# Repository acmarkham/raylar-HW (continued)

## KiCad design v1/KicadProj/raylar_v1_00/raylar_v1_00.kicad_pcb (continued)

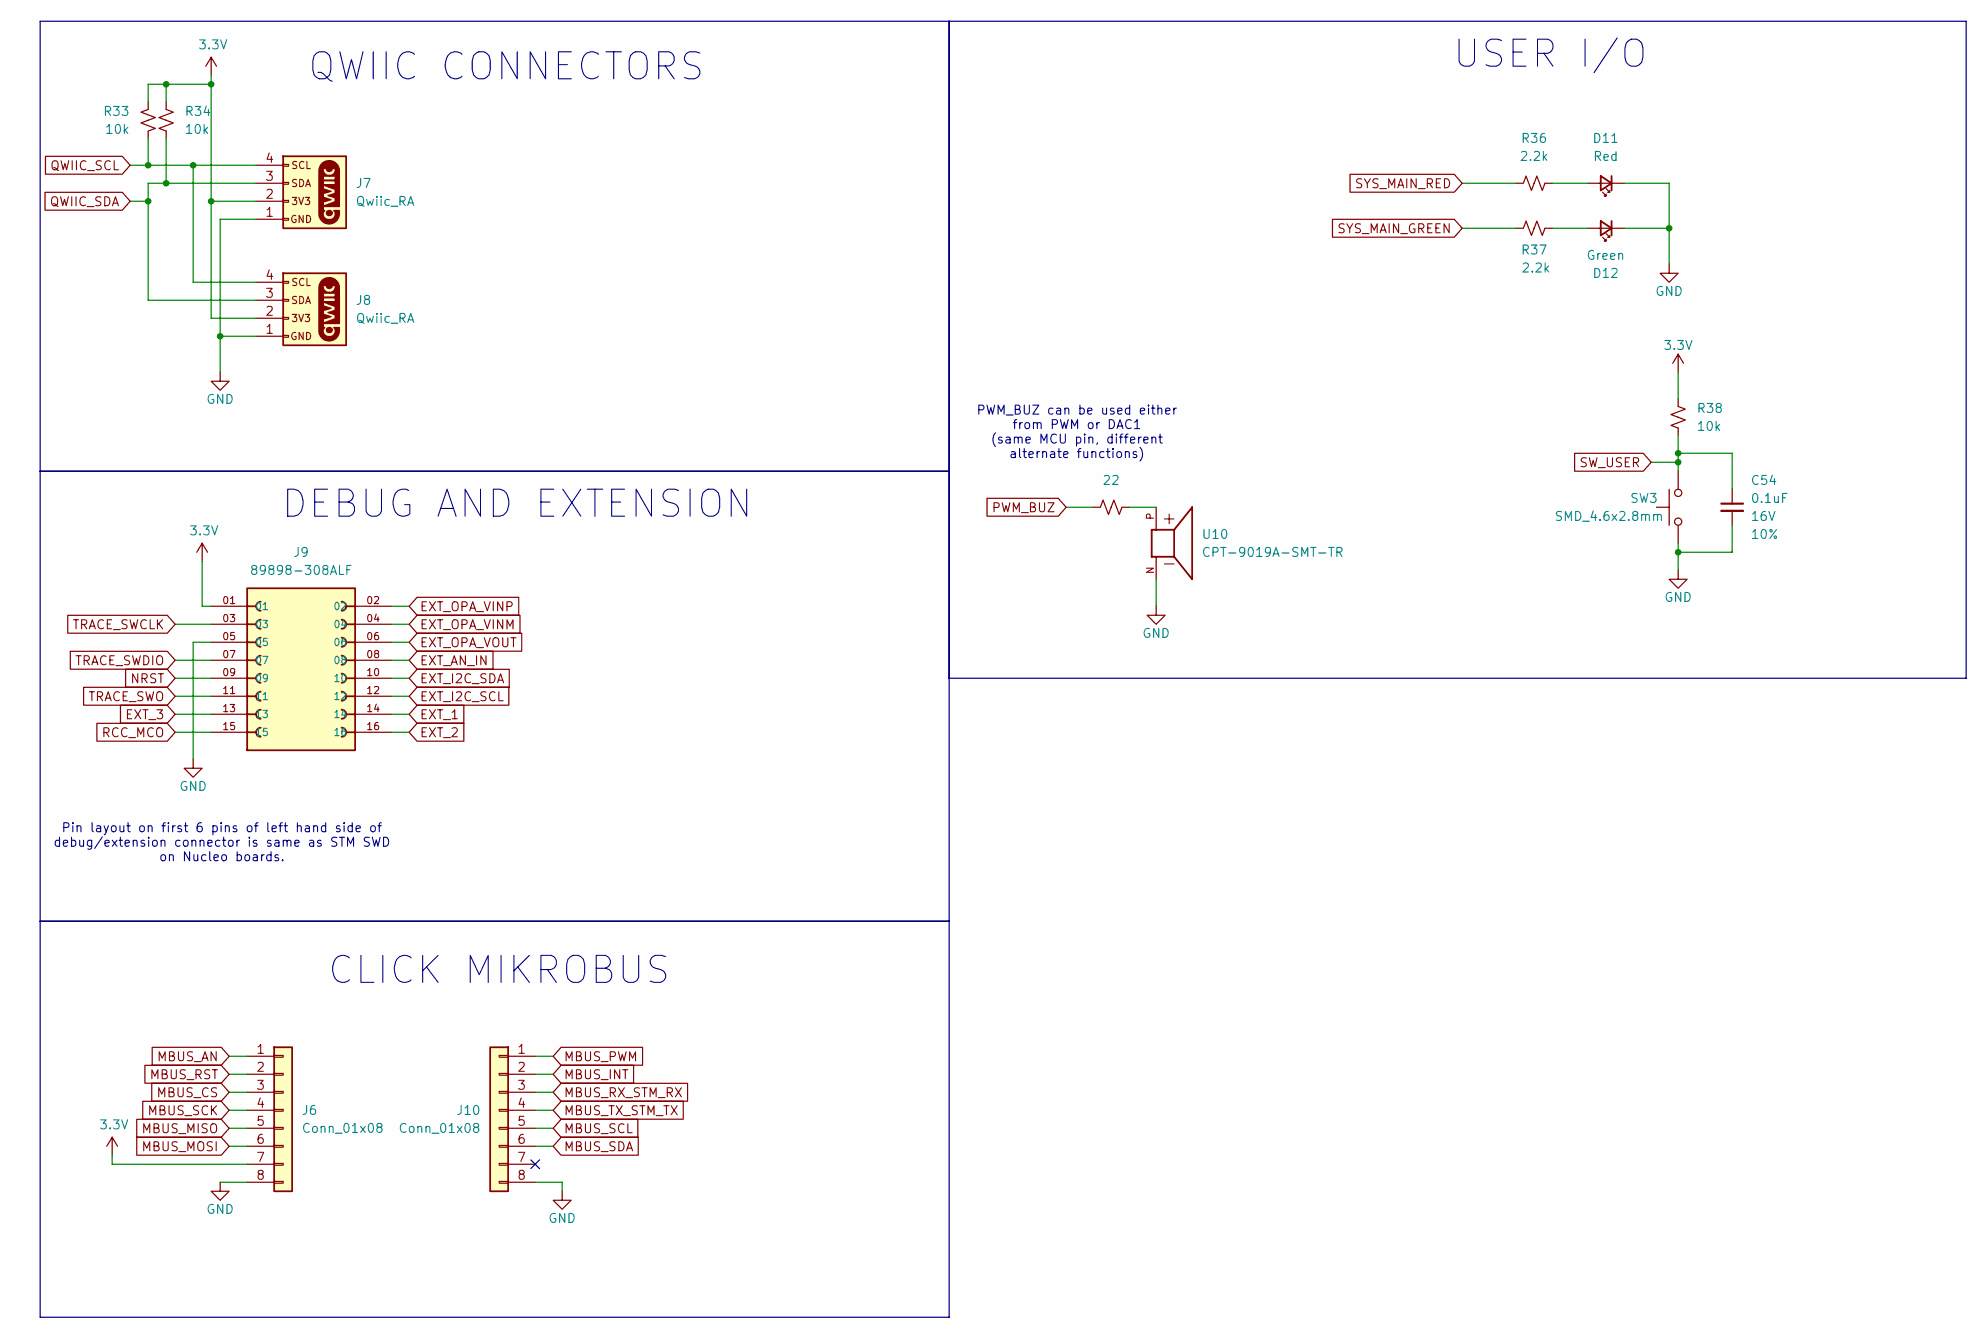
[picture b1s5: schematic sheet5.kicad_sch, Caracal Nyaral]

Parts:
C54: 0.1uF; C_0402_1005Metric; Voltage 16V; Tolerance 10%; LCSC C77020
D11: Red; LED_0603_1608Metric_Red; LCSC C19171390
D12: Green; LED_0603_1608Metric_Green; LCSC C19273151
J6, J10: Conn_01x08; 1x08_P2.54mm_Socket_Vertical_SMD_Pin1RightDown; Digikey 2073-BG125-08-A-1-1-0440-N-D-ND
J7, J8: Qwiic_RA; JST_1x04_P1.0mm_Horizontal_SMD; Digikey 455-SM04B-SRSS-TBDKR-ND
J9: 89898-308ALF; AMPHENOL_89898-308ALF; PARTREV AK; Digikey 609-5158-6-ND
R33, R34, R38: 10k; R_0402_1005Metric; LCSC C60489
R35: 22; R_0402_1005Metric; LCSC C25092
R36, R37: 2.2k; R_0402_1005Metric; LCSC C25879
SW3: SMD_4.6x2.8mm; Push_SMD_4.6x2.8mm_h1.9mm; Mfg Part# KMR231NGLFS; LCSC C221676
U10: CPT-9019A-SMT-TR; XDCR_CPT-9019A-SMT-TR; PARTREV 1.0; LCSC C20181991

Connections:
3.3V: J6.7, J7.2, J8.2, J9.01, R33.2, R34.2, R38.2; also elsewhere on the board
EXT_1: J9.14; also elsewhere on the board
EXT_2: J9.16; also elsewhere on the board
EXT_3: J9.13; also elsewhere on the board
EXT_AN_IN: J9.08; also elsewhere on the board
EXT_I2C_SCL: J9.12; also elsewhere on the board
EXT_I2C_SDA: J9.10; also elsewhere on the board
EXT_OPA_VINM: J9.04; also elsewhere on the board
EXT_OPA_VINP: J9.02; also elsewhere on the board
EXT_OPA_VOUT: J9.06; also elsewhere on the board
GND: C54.2, D11.1 (K), D12.1 (K), J6.8, J7.1, J8.1, J9.05, J10.8, SW3.1, U10.N; also elsewhere on the board
MBUS_AN: J6.1; also elsewhere on the board
MBUS_CS: J6.3; also elsewhere on the board
MBUS_INT: J10.2; also elsewhere on the board
MBUS_MISO: J6.5; also elsewhere on the board
MBUS_MOSI: J6.6; also elsewhere on the board
MBUS_PWM: J10.1; also elsewhere on the board
MBUS_RST: J6.2; also elsewhere on the board
MBUS_RX_STM_RX: J10.3; also elsewhere on the board
MBUS_SCK: J6.4; also elsewhere on the board
MBUS_SCL: J10.5; also elsewhere on the board
MBUS_SDA: J10.6; also elsewhere on the board
MBUS_TX_STM_TX: J10.4; also elsewhere on the board
NRST: J9.09; also elsewhere on the board
unnamed: D11.2 (A), R36.2
unnamed: D12.2 (A), R37.2
unnamed: R35.2, U10.P
PWM_BUZ: R35.1; also elsewhere on the board
QWIIC_SCL: J7.4, J8.4, R33.1; also elsewhere on the board
QWIIC_SDA: J7.3, J8.3, R34.1; also elsewhere on the board
RCC_MCO: J9.15; also elsewhere on the board
SW_USER: C54.1, R38.1, SW3.2; also elsewhere on the board
SYS_MAIN_GREEN: R37.1; also elsewhere on the board
SYS_MAIN_RED: R36.1; also elsewhere on the board
TRACE_SWCLK: J9.03; also elsewhere on the board
TRACE_SWDIO: J9.07; also elsewhere on the board
TRACE_SWO: J9.11; also elsewhere on the board

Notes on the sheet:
Pin layout on first 6 pins of left hand side of debug/extension connector is same as STM SWD on Nucleo boards.
PWM_BUZ can be used either from PWM or DAC1 (same MCU pin, different alternate functions)
DEBUG AND EXTENSION
CLICK MIKROBUS
USER I/O
QWIIC CONNECTORS

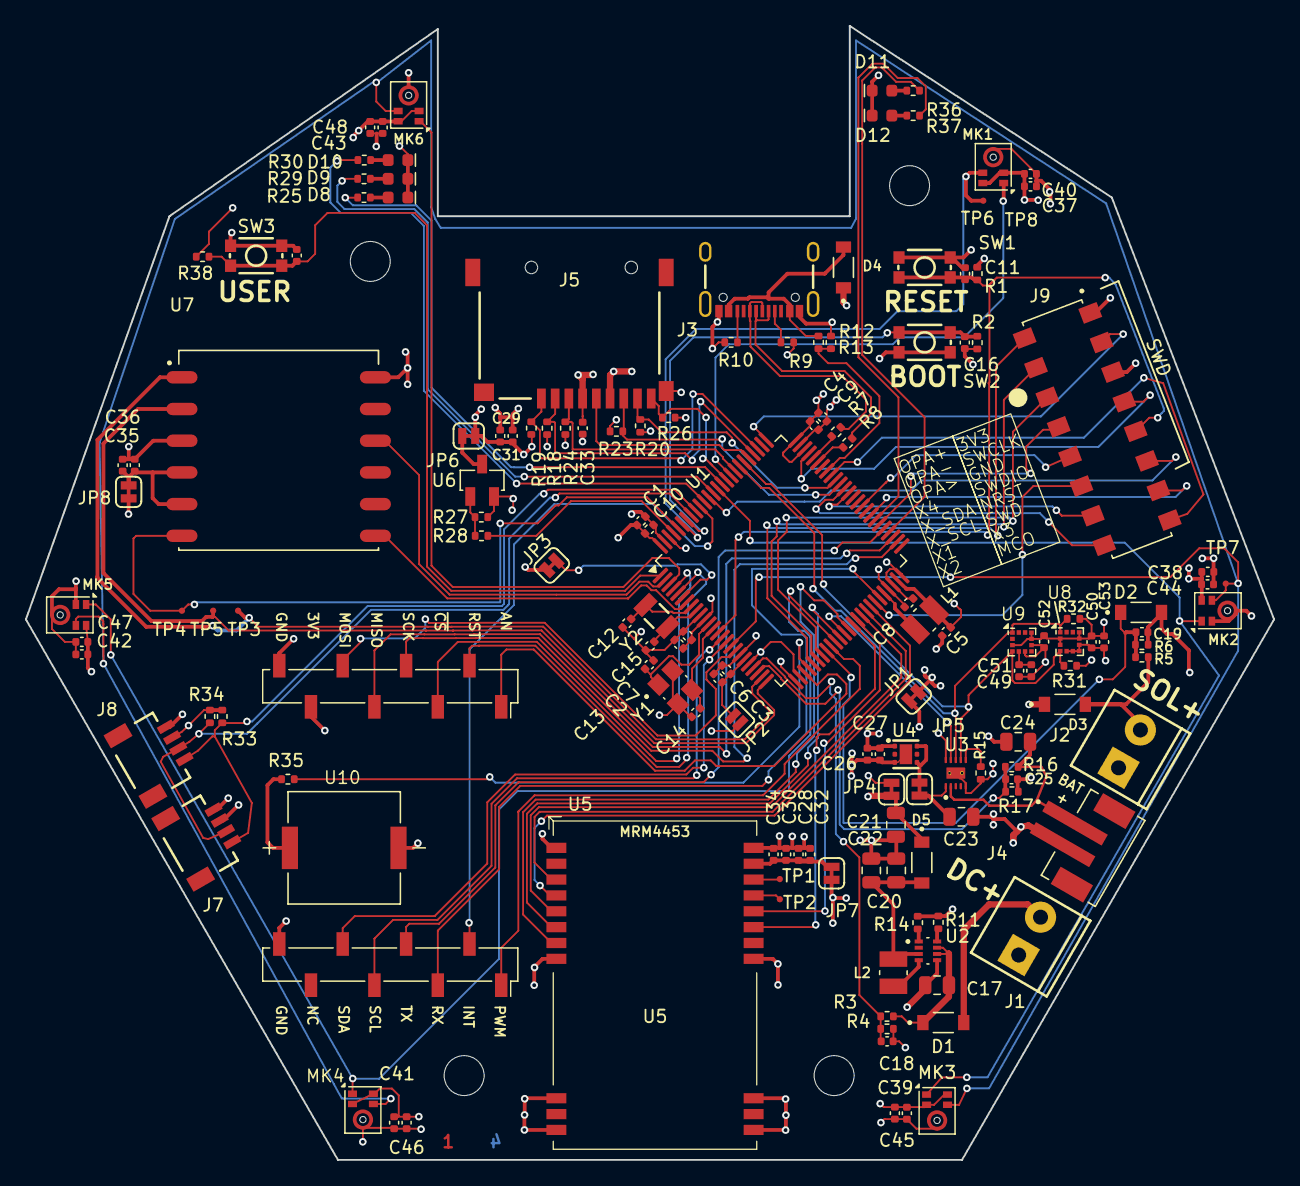
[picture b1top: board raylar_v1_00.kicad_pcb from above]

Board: 4 copper layers, 100.0 x 90.9 mm, 149 parts (0 on the bottom side), 114 nets.

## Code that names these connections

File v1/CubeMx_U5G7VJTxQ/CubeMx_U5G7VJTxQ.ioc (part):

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Mcu.Name=STM32U5G7VJTxQ
Mcu.Package=LQFP100
Mcu.UserName=STM32U5G7VJTxQ
PA0.Mode=IN5-Single-Ended
PA0.Signal=ADC2_IN5
PA1.Mode=IN6-Single-Ended
PA1.Signal=ADC2_IN6
PA11.GPIOParameters=GPIO_Label
PA11.GPIO_Label=USB_DM
PA11.Mode=Internal_Phy_Device
PA11.Signal=USB_OTG_HS_DM
PA12.GPIOParameters=GPIO_Label
PA12.GPIO_Label=USB_DP
PA12.Mode=Internal_Phy_Device
PA12.Signal=USB_OTG_HS_DP
PA13\ (JTMS/SWDIO).GPIOParameters=GPIO_Label
PA13\ (JTMS/SWDIO).GPIO_Label=TRACE_SWDIO
PA13\ (JTMS/SWDIO).Mode=Trace_Asynchronous_SW
PA13\ (JTMS/SWDIO).Signal=DEBUG_JTMS-SWDIO
PA14\ (JTCK/SWCLK).GPIOParameters=GPIO_Label
PA14\ (JTCK/SWCLK).GPIO_Label=TRACE_SWCLK
PA14\ (JTCK/SWCLK).Mode=Trace_Asynchronous_SW
PA14\ (JTCK/SWCLK).Signal=DEBUG_JTCK-SWCLK
PA2.GPIOParameters=GPIO_Label
PA2.GPIO_Label=GPS_RX_STM_TX
PA2.Mode=Asynchronous
PA2.Signal=USART2_TX
PA3.GPIOParameters=GPIO_Label
PA3.GPIO_Label=GPS_TX_STM_RX
PA3.Mode=Asynchronous
PA3.Signal=USART2_RX
PA4.GPIOParameters=GPIO_Label
PA4.GPIO_Label=MBUS_AN
PA4.Mode=IN9-Single-Ended
PA4.Signal=ADC2_IN9
PA5.GPIOParameters=GPIO_Label
PA5.GPIO_Label=BUZ
PA5.Signal=SharedStack_PA5
PA5.Stacked=true
PA6.GPIOParameters=GPIO_Label
PA6.GPIO_Label=EXT_OPA_VINP
PA6.Mode=Standalone
PA6.Signal=OPAMP2_VINP
PA7.GPIOParameters=GPIO_Label
PA7.GPIO_Label=EXT_OPA_VINM
PA7.Mode=Standalone
PA7.Signal=OPAMP2_VINM
PA8.Mode=Clock-out
PA8.Signal=RCC_MCO
PA9.GPIOParameters=GPIO_Label
PA9.GPIO_Label=USB_VBUS
PA9.Mode=Activate_VBUS_FS
PA9.Signal=USB_OTG_HS_VBUS
PB0.GPIOParameters=GPIO_Label
PB0.GPIO_Label=EXT_OPA_VOUT
PB0.Mode=Standalone
PB0.Signal=OPAMP2_VOUT
PB1.Mode=IN16-Single-Ended
PB1.Signal=ADC2_IN16
PB10.GPIOParameters=GPIO_Label
PB10.GPIO_Label=EXT_I2C_SCL
PB10.Mode=I2C
PB10.Signal=I2C4_SCL
PB11.GPIOParameters=GPIO_Label
PB11.GPIO_Label=MBUS_RX_STM_RX
PB11.Mode=Asynchronous
PB11.Signal=USART3_RX
PB13.GPIOParameters=GPIO_Label
PB13.GPIO_Label=MBUS_SCK
PB13.Mode=Full_Duplex_Master
PB13.Signal=SPI2_SCK
PB14.GPIOParameters=GPIO_Label
PB14.GPIO_Label=MBUS_MISO
PB14.Mode=Full_Duplex_Master
PB14.Signal=SPI2_MISO
PB2.GPIOParameters=GPIO_Label
PB2.GPIO_Label=MBUS_PWM
PB2.Mode=PWM Generation4 CH4N
PB2.Signal=TIM8_CH4N
PB3\ (JTDO/TRACESWO).GPIOParameters=GPIO_Label
PB3\ (JTDO/TRACESWO).GPIO_Label=TRACE_SWO
PB3\ (JTDO/TRACESWO).Mode=Trace_Asynchronous_SW
PB3\ (JTDO/TRACESWO).Signal=DEBUG_JTDO-SWO
PB4\ (NJTRST).GPIOParameters=GPIO_Label
PB4\ (NJTRST).GPIO_Label=EXT_3
PB4\ (NJTRST).Signal=GPIO_Output
PB5.GPIOParameters=GPIO_Label
PB5.GPIO_Label=SYS_MAIN_RED
PB5.Signal=GPIO_Output
PB6.GPIOParameters=GPIO_Label
PB6.GPIO_Label=QWIIC_SCL
PB6.Mode=I2C
PB6.Signal=I2C1_SCL
PB7.GPIOParameters=GPIO_Label
PB7.GPIO_Label=QWIIC_SDA
PB7.Mode=I2C
PB7.Signal=I2C1_SDA
PB8.GPIOParameters=GPIO_Label
PB8.GPIO_Label=MIC_CCLK0
PB8.Mode=MOD_MDF_CCK0
PB8.Signal=MDF1_CCK0
PB9.GPIOParameters=GPIO_Label
PB9.GPIO_Label=GPS_PPS
PB9.Signal=S_TIM4_CH4
PB9.Stacked=true
PC0.GPIOParameters=GPIO_Label
PC0.GPIO_Label=MBUS_SCL
PC0.Mode=I2C
PC0.Signal=I2C3_SCL
PC1.GPIOParameters=GPIO_Label
PC1.GPIO_Label=MBUS_SDA
PC1.Mode=I2C
PC1.Signal=I2C3_SDA
PC10.GPIOParameters=GPIO_Label
PC10.GPIO_Label=SDIO_D2
PC10.Mode=SD_4_bits_Wide_bus
PC10.Signal=SDMMC1_D2
PC11.GPIOParameters=GPIO_Label
PC11.GPIO_Label=SDIO_D3
PC11.Mode=SD_4_bits_Wide_bus
PC11.Signal=SDMMC1_D3
PC12.GPIOParameters=GPIO_Label
PC12.GPIO_Label=SDIO_CLK
PC12.Mode=SD_4_bits_Wide_bus
PC12.Signal=SDMMC1_CK
PC13.GPIOParameters=GPIO_Label
PC13.GPIO_Label=GPS_RST
PC13.Signal=GPIO_Output
PC14-OSC32_IN\ (PC14).GPIOParameters=GPIO_Label
PC14-OSC32_IN\ (PC14).GPIO_Label=OSC_32K_IN
PC14-OSC32_IN\ (PC14).Mode=LSE-External-Oscillator
PC14-OSC32_IN\ (PC14).Signal=RCC_OSC32_IN
PC15-OSC32_OUT\ (PC15).GPIOParameters=GPIO_Label
PC15-OSC32_OUT\ (PC15).GPIO_Label=OSC_32K_OUT
PC15-OSC32_OUT\ (PC15).Mode=LSE-External-Oscillator
PC15-OSC32_OUT\ (PC15).Signal=RCC_OSC32_OUT
PC2.GPIOParameters=GPIO_Label
PC2.GPIO_Label=MIC_CCLK1
PC2.Mode=MOD_MDF_CCK1
PC2.Signal=MDF1_CCK1
PC3.GPIOParameters=GPIO_Label
PC3.GPIO_Label=MBUS_MOSI
PC3.Mode=Full_Duplex_Master
PC3.Signal=SPI2_MOSI
PC6.GPIOParameters=GPIO_Label
PC6.GPIO_Label=SYS_RF_GREEN
PC6.Signal=GPIO_Output
PC7.GPIOParameters=GPIO_Label
PC7.GPIO_Label=SYS_RF_RED
PC7.Signal=GPIO_Output
PC8.GPIOParameters=GPIO_Label
PC8.GPIO_Label=SDIO_D0
PC8.Mode=SD_4_bits_Wide_bus
PC8.Signal=SDMMC1_D0
PC9.GPIOParameters=GPIO_Label
PC9.GPIO_Label=SDIO_D1
PC9.Mode=SD_4_bits_Wide_bus
PC9.Signal=SDMMC1_D1
PD0.GPIOParameters=GPIO_Label
PD0.GPIO_Label=SENS_I2C_SDA
PD0.Mode=I2C
PD0.Signal=I2C5_SDA
PD1.GPIOParameters=GPIO_Label
PD1.GPIO_Label=SENS_I2C_SCL
PD1.Mode=I2C
PD1.Signal=I2C5_SCL
PD12.Signal=ADC4_IN16
PD13.GPIOParameters=GPIO_Label
PD13.GPIO_Label=EXT_I2C_SDA
PD13.Mode=I2C
PD13.Signal=I2C4_SDA
PD14.GPIOParameters=GPIO_Label
PD14.GPIO_Label=SYS_GPS_GREEN
PD14.Signal=GPIO_Output
PD15.GPIOParameters=GPIO_Label
PD15.GPIO_Label=SYS_GPS_RED
PD15.Signal=GPIO_Output
PD2.GPIOParameters=GPIO_Label
PD2.GPIO_Label=SDIO_CMD
PD2.Mode=SD_4_bits_Wide_bus
PD2.Signal=SDMMC1_CMD
PD3.GPIOParameters=GPIO_Label
PD3.GPIO_Label=MIC_SD0
PD3.Mode=MOD_MDF_SITF0_CCK0
PD3.Signal=MDF1_SDI0
PD4.GPIOParameters=GPIO_Label
PD4.GPIO_Label=SD_SW
PD4.Signal=GPIO_Output
PD6.GPIOParameters=GPIO_Label
PD6.GPIO_Label=MIC_SD1
PD6.Mode=MOD_MDF_SITF1_CCK1
PD6.Signal=MDF1_SDI1
PD8.GPIOParameters=GPIO_Label
PD8.GPIO_Label=MBUS_TX_STM_TX
PD8.Mode=Asynchronous
PD8.Signal=USART3_TX
PE0.GPIOParameters=GPIO_Label
PE0.GPIO_Label=SD_PWR
PE0.Signal=GPIO_Output
PE10.GPIOParameters=GPIO_Label
PE10.GPIO_Label=RF_BUSY
PE10.Signal=GPIO_Input
PE11.GPIOParameters=GPIO_Label
PE11.GPIO_Label=RF_NRST
PE11.Signal=GPIO_Output
PE12.GPIOParameters=GPIO_Label
PE12.GPIO_Label=RF_IRQ
PE12.Signal=GPXTI12
PE13.GPIOParameters=GPIO_Label
PE13.GPIO_Label=RF_SCK
PE13.Mode=Full_Duplex_Master
PE13.Signal=SPI1_SCK
PE14.GPIOParameters=GPIO_Label
PE14.GPIO_Label=RF_MISO
PE14.Mode=Full_Duplex_Master
PE14.Signal=SPI1_MISO
PE15.GPIOParameters=GPIO_Label
PE15.GPIO_Label=RF_MOSI
PE15.Mode=Full_Duplex_Master
PE15.Signal=SPI1_MOSI
PE2.GPIOParameters=GPIO_Label
PE2.GPIO_Label=SW_USER
PE2.Signal=GPIO_Output
PE3.GPIOParameters=GPIO_Label
PE3.GPIO_Label=GPS_EN
PE3.Signal=GPIO_Output
PE4.GPIOParameters=GPIO_Label
PE4.GPIO_Label=MIC_SD3
PE4.Mode=MOD_MDF_SITF3_CCK1
PE4.Signal=MDF1_SDI3
PE5.GPIOParameters=GPIO_Label
PE5.GPIO_Label=MBUS_CS
PE5.Signal=GPIO_Output
PE6.GPIOParameters=GPIO_Label
PE6.GPIO_Label=MBUS_RST
PE6.Signal=GPIO_Output
PE7.GPIOParameters=GPIO_Label
PE7.GPIO_Label=MIC_SD2
PE7.Mode=MOD_MDF_SITF2_CCK1
PE7.Signal=MDF1_SDI2
PE8.GPIOParameters=GPIO_Label
PE8.GPIO_Label=RF_CS
PE8.Signal=GPIO_Output
PH0-OSC_IN\ (PH0).GPIOParameters=GPIO_Label
PH0-OSC_IN\ (PH0).GPIO_Label=HSE_OSC_IN
PH0-OSC_IN\ (PH0).Mode=HSE-External-Oscillator
PH0-OSC_IN\ (PH0).Signal=RCC_OSC_IN
PH1-OSC_OUT\ (PH1).GPIOParameters=GPIO_Label
PH1-OSC_OUT\ (PH1).GPIO_Label=HE_OSC_OUT
PH1-OSC_OUT\ (PH1).Mode=HSE-External-Oscillator
PH1-OSC_OUT\ (PH1).Signal=RCC_OSC_OUT
PH3-BOOT0.GPIOParameters=GPIO_Label
PH3-BOOT0.GPIO_Label=BOOT0
PH3-BOOT0.Signal=GPIO_Input
RCC.HSE_VALUE=16000000
RCC.SYSCLKFreq_VALUE=64000000
RCC.SYSCLKSource=RCC_SYSCLKSOURCE_PLLCLK
board=custom

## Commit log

2026-05-07 Updated fab
2026-05-13 Updated readme, magic scripts for exporting schematic and board renders
2026-05-13 slashes on reamde
